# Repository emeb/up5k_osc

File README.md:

# up5k_osc
An FPGA-based digital oscillator for Eurorack

## What is it?
up5k_osc is a Eurorack-format digital oscillator demonstrating digital
audio synthesis with a low-cost FPGA. It supports several basic waveforms
commonly found in analog synthesizers, but generated digitally at very high
sample rates to avoid many of the problems with aliasing that occur when
these waveforms are synthesized at lower sample rates.

## Features
​
* 12HP wide 3U standard Eurorack module
* +/-12V supply on Doepfer-standard 16-pin shrouded, keyed header (30ma max)
* Trimmed 1V/Oct pitch control input with coarse and fine adjustment pots
* Attenuated Exponential FM input
* 3 additional uncommited +/-5V CV inputs with associated setting pots
* Sync input
* Two +/-5V range audio outputs
* Three 3 position toggles for range and mode control
* RGB LED indicator
* Additional single LED indicator
* USB-based firmware updates

## Design details
* Lattice iCE40 Ultra Plus 5k FPGA
* 4MB SPI Flash memory for configuration data, firmware and tables.
* 4-channel 12-bit SPI ADC with 500kSPS max sample rate
* Direct-access SPI Programming header
* 3-pin diagnostic header (2 data + ground)
* Reset and Bootloader pushbuttons
* Done Program LED
* Buck SMPS regulator for low current draw from +12V supply
* Differential PDM DACs for high-resolution, high sample rate and low THD audio

## Resources
* [Schematic](docs/up5k_osc_schematic.pdf)
* [BOM](docs/up5k_osc_bom.ods)

## Motivation
One of the most thorny issues encountered when attempting to synthesize simple
analog waveforms in the digital domain is that of aliasing which occurs due
to sharp transitions coupled with low sample rates. Seemingly "obvious" methods
of generating simple waveforms like sawtooths and square or pulse waves fail
miserably when the sharp edges of these waveforms jitter around due to the low
timing resolution of practical DSP sample rates. Mountains of research have been
devoted to DSP approaches to minimizing this edge jitter using techniques such
as BLIT, BLEP, MinBLEP, PolyBLEP, DPW, etc. These work, but end up becoming
compromises between the complexity of the approach (and the consequent CPU load
they impose) and the degree of alias rejection that they provide.

The brute-force approach is to synthesize these analog waveforms at sufficiently
high sample rates that the timing jitter becomes imperceptible. This is the
method that up5k_osc uses - an audio-rate oscillator is synthesized at sample
rates in excess of 10MHz which knocks the aliases of even the buzziest narrow
pulse wave down below 80dBfs. Differential Pulse Density Modulation is used to
do the digital-to-analog conversion in an inexpensive yet highly linear fashion.

## Theory of Operation
The up5k_osc system comprises a power supply, ADC, Flash Memory, FPGA and analog
I/O processing. 

### Power Supply
Eurorack systems typically provide +/-12V rails at a minimum, and as DSP becomes
a more common feature in typical racks, the +12V rails are disproportionally
loaded down by the use of simple LDO linear regulators to supply the high currents
needed by most modern digital components. up5k_osc uses a SMPS regulator module
to efficiently provide an internal 5V supply from which 3.3V analog and digital
supplys can be derived with less heat and waste.

### Analog Input Processing
A 4-channel 12-bit 500kSPS SPI ADC is used to digitize control voltage inputs
to the up5k_osc. One channel is dedicated to handling the typical 1V/Oct pitch
control and includes trimming to calibrate the 1V/Oct slope, as well as coarse
and fine user offsets as well as summing an attenuated FM input. This provides
roughly 2.7cents/lsb pitch resolution over a 10V range which covers most of
the musical range to an accuracy better than the commonly accepted human
perception.

The other three ADC channels are uncommitted CV inputs with offset controls and
a 10Vpp range. Running that the maximum rated conversion speed, the ADC can
provide 125kSPS per channel which is sufficiently high to provide good temporal
resolution.

### FPGA and SPI Flash
The Lattice iCE40 Ultra Plus 5k FPGA provides a modest gate count, a number of
useful hard IP cores, including SPI, I2C, Multiply-Accumulate and large RAM.
These resources are sufficient for reasonably complex DSP, soft processor cores
and I/O tasks. In the up5k_osc, the FPGA is loaded from the SPI Flash at power
up and immediately begins execution of a basic processing pipeline which begins
with driving a continuous stream of conversions from the ADC, formatting the
results for control of a fast internal NCO, waveshaping and then finally
generating the PDM output signals.

FPGA bitstreams, along with soft processor firmware and synthesis tables are
stored in the SPI flash. During development it's often simplest to directly load
the FPGA over the SPI configuration bus via a programming dongle and header on
the board, bypassing the SPI flash. In end-use situations however it's desirable
to have a simpler approach, and for that purpose a USB interface is provided
which uses the NO2 bootloader and the standardized DFU protocol to load data
into the SPI flash without extra hardware.

[NO2 Bootloader](https://github.com/no2fpga/no2bootloader)

The up5k_osc FPGA pinout for USB, SPI Flash and boot select button + LED has
been designed to follow that of the icebreaker bitsy, so building the
bootloader with that configuration will generate a usable bitstream.

### Switches and LEDs
User control options are provided in the form of three 3-position SPDT toggles
(on-off-on) which can be used to set pitch range, waveform types, etc. A few
LEDs are also provided to indicate operating conditions.

### Analog Outputs
Two PDM DACs are available with fully differential inputs from the FPGA to
improve linearity despite mismatches in rise & fall timing. A two-stage
lowpass reconstruction filter rolls off at about 30kHz, allowing harmonic
content well above normal human hearing range. SNR has been observed as better
that 90dBfs, THD for 1kHz sine is better than 80dBfs and with 16MSPS sample
rates the aliasing on naive sawtooth waveforms are lower than 80dBfs beyond
10kHz. Output levels of 10Vpp are compatible with common Eurorack standards.

## Gateware
Demonstration gateware for the up5k_osc is provided which handles all the basic
functions of an oscillator. Three pitch ranges are provided which cover rates
from 13min/cycle to 10kHz. Two output waveforms can be selected from among
sine/saw/pulse, with pulsewidth controlled by one of the CV inputs.

As delivered the demo gateware does not use a soft processor core. A serial
diagnostic output is generated by simple state machine logic to provide
observation of the ADC conversion results (formatted as 115k 8N1 serial). An
alternate build is possible via macro definitions in the source code that
enables a RISC-V core that can do more complex diagnostics, or even control
the oscillator with some imagination and more coding.

## Future Work
Going beyond this is certainly possible - wavetable morphing has been tested and
other synthesis techniques such as multi-operator FM are possible. The USB
interface could be employed to turn the module into an Audio class peripheral
that handles MIDI or PCM audio.

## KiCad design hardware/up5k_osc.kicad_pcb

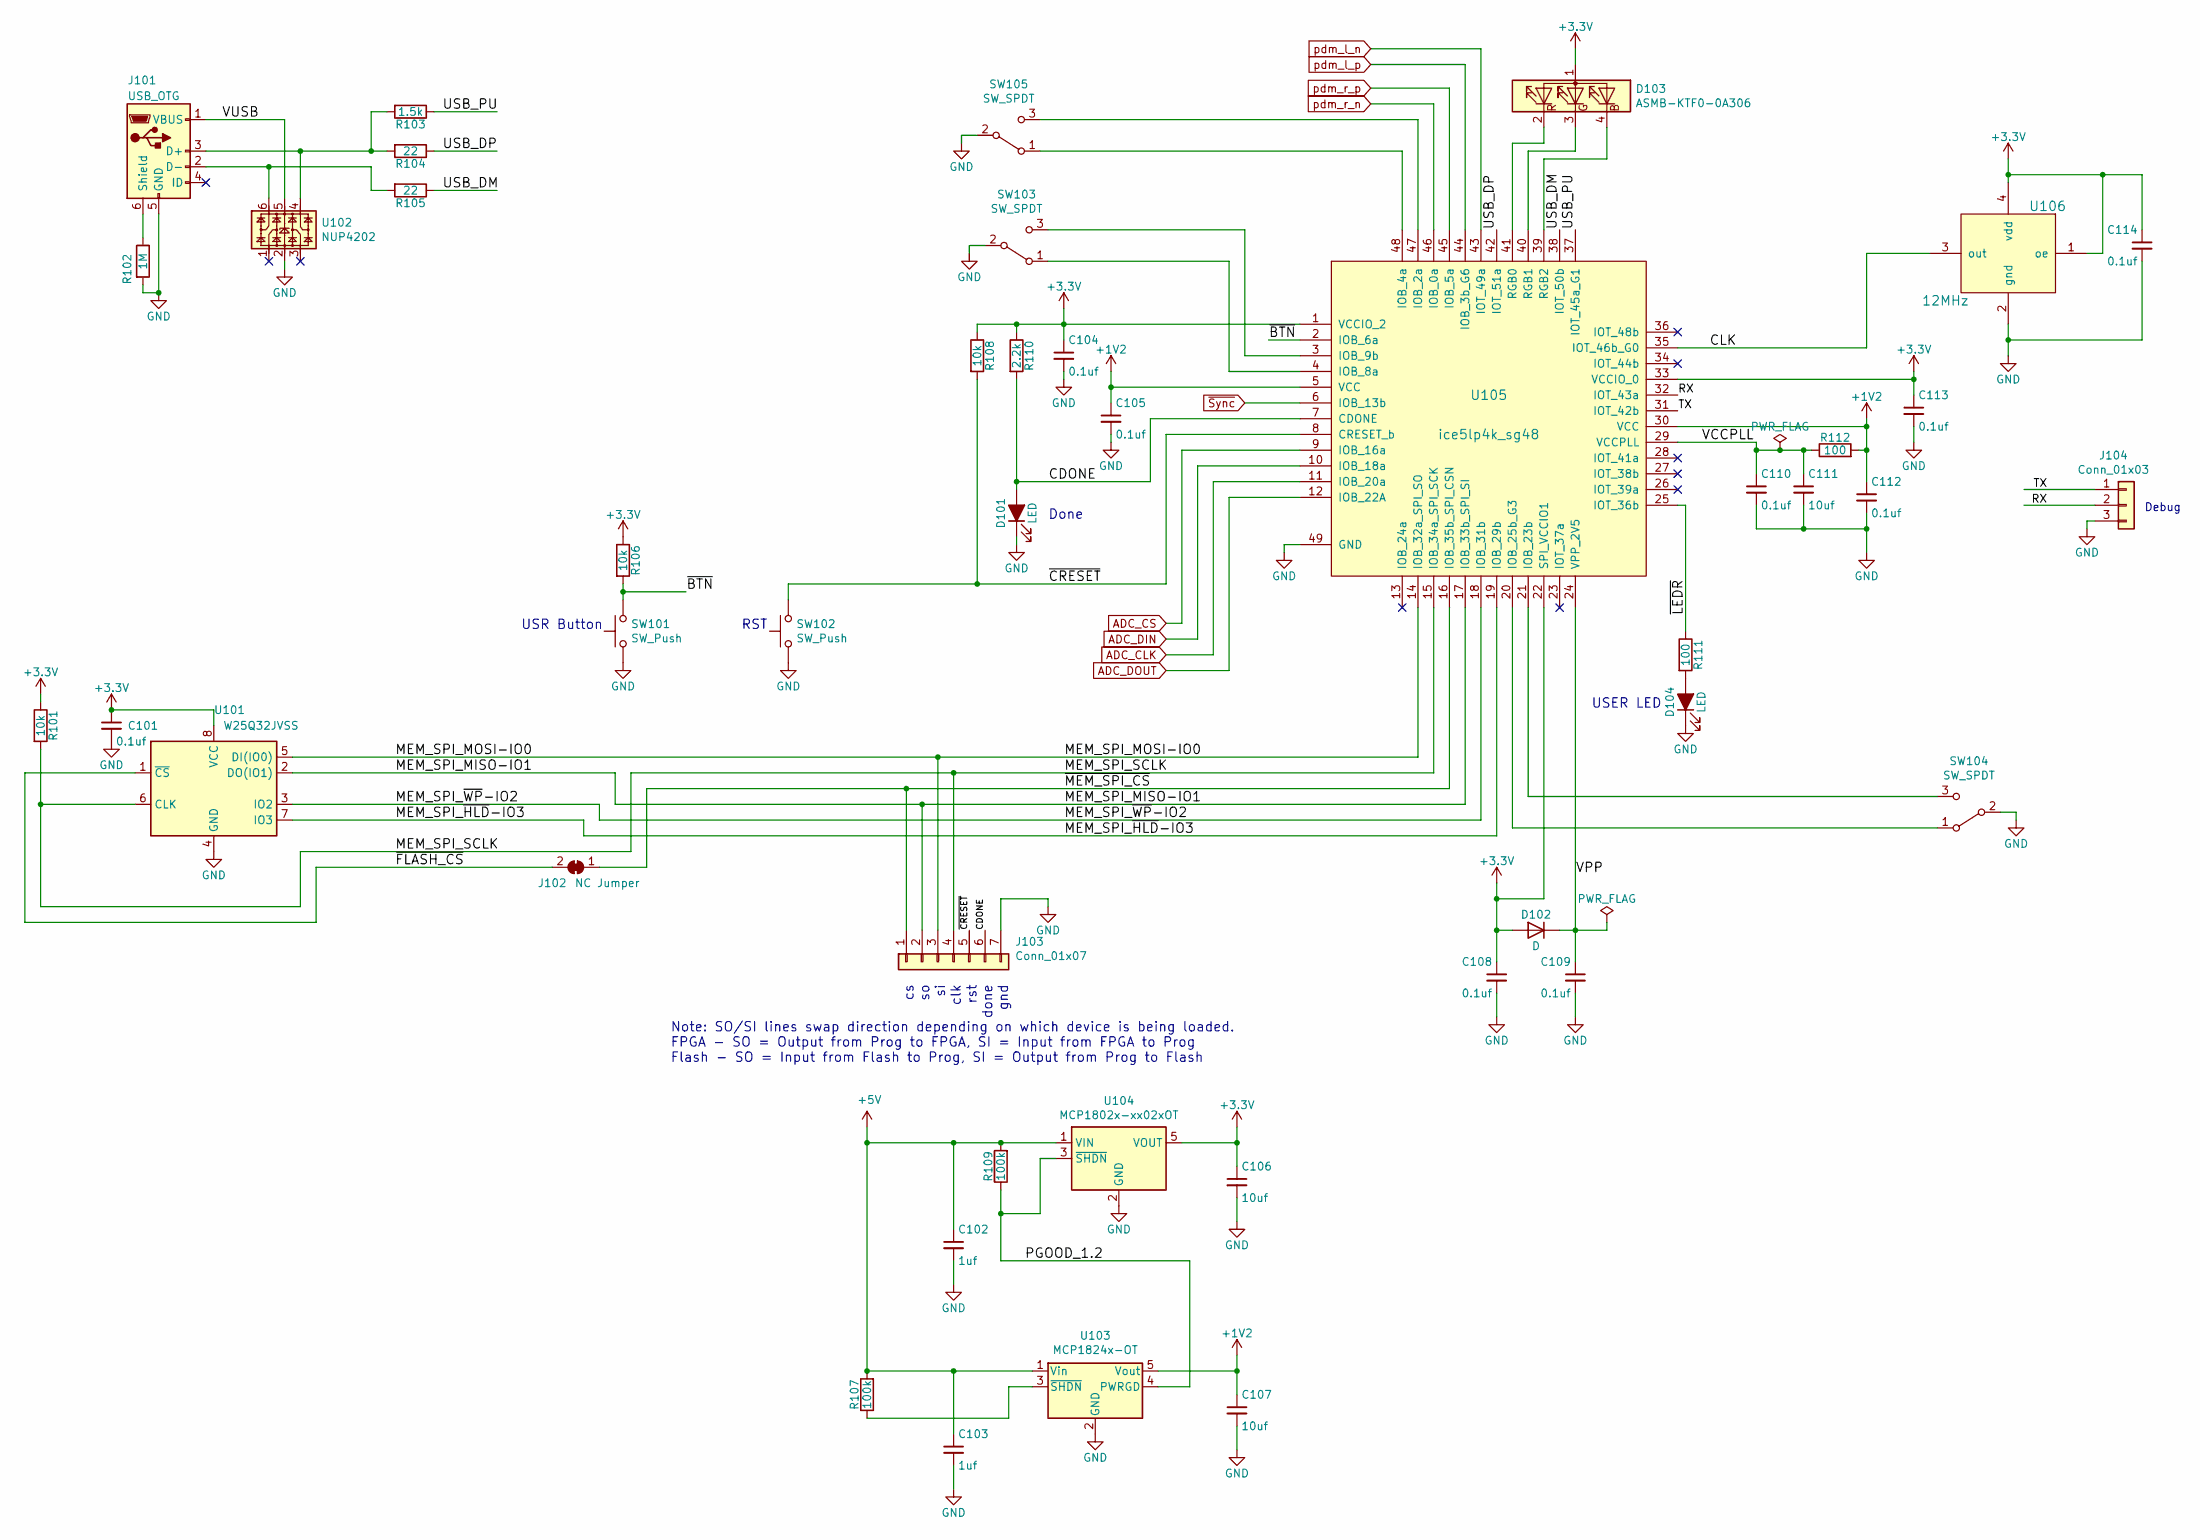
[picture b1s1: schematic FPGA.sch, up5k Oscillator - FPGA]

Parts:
C101, C104, C105, C108, C109, C110, C112, C113, C114: 0.1uf; C_0603
C102, C103: 1uf; C_0603
C106, C107, C111: 10uf; C_0805
D101, D104: LED; LED_0603
D102: D; D_0603
D103: ASMB-KTF0-0A306‎
J101: USB_OTG; USB_Micro-B_10103594-0001LF_actual_outline
J102: NC Jumper; SolderJumper-2_P1.3mm_Bridged_RoundedPad1.0x1.5mm
J103: Conn_01x07; Pin_Header_Straight_1x07_Pitch2.54mm
J104: Conn_01x03; Pin_Header_Straight_1x03_Pitch2.54mm
R101, R106, R108: 10k; R_0603
R102: 1M; R_0603
R103: 1.5k; R_0603
R104, R105: 22; R_0603
R107, R109: 100k; R_0603
R110: 2.2k; R_0603
R111, R112: 100; R_0603
SW101, SW102: SW_Push; SW_SPST_KMR2
SW103, SW104, SW105: SW_SPDT; SPDT_Submini
U101: W25Q32JVSS; SOIC-8_3.9x4.9mm_Pitch1.27mm
U102: NUP4202; SOT-23-6
U103: MCP1824x-OT; SOT-23-5
U104: MCP1802x-xx02xOT; SOT-23-5
U105: ice5lp4k_sg48; QFN-48-1EP_7x7mm_Pitch0.5mm_DIY_PADS
U106: 12MHz; Oscillator_SMD_SeikoEpson_SG210-4pin_2.5x2.0mm

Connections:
+1V2: C105.1, C107.1, C112.1, R112.2, U103.5 (Vout), U105.5 (VCC), U105.30 (VCC)
+3V3: C101.1, C104.1, C106.1, C108.1, C113.1, C114.1, D102.2 (A), D103.1 (A), R101.1, R106.1, R108.1, R110.1, U101.8 (VCC), U104.5 (VOUT), U105.1 (VCCIO_2), U105.22 (SPI_VCCIO1), U105.33 (VCCIO_0), U106.1 (oe), U106.4 (vdd); also elsewhere on the board
+5V: C102.1, C103.1, R107.2, R109.2, U103.1 (Vin), U104.1 (VIN); also elsewhere on the board
/Sheet60703823/CDONE: D101.2 (A), J103.6, R110.2, U105.7 (CDONE)
/Sheet60703823/CLK: U105.35 (IOT_46b_G0), U106.3 (out)
/Sheet60703823/MEM_SPI_MISO-IO1: J103.2, U101.2 (DO(IO1)), U105.17 (IOB_33b_SPI_SI)
/Sheet60703823/MEM_SPI_MOSI-IO0: J103.3, U101.5 (DI(IO0)), U105.14 (IOB_32a_SPI_SO)
/Sheet60703823/MEM_SPI_SCLK: J103.4, R101.2, U101.6 (CLK), U105.15 (IOB_34a_SPI_SCK)
/Sheet60703823/MEM_SPI_~HLD~-IO3: U101.7 (IO3), U105.19 (IOB_29b)
/Sheet60703823/MEM_SPI_~WP~-IO2: U101.3 (IO2), U105.18 (IOB_31b)
/Sheet60703823/PGOOD_1.2: R109.1, U103.4 (PWRGD), U104.3 (~SHDN)
/Sheet60703823/RX: J104.2, U105.32 (IOT_43a)
/Sheet60703823/TX: J104.1, U105.31 (IOT_42b)
/Sheet60703823/USB_DM: R105.1, U105.38 (IOT_50b)
/Sheet60703823/USB_DP: R104.1, U105.42 (IOT_51a)
/Sheet60703823/USB_PU: R103.1, U105.37 (IOT_45a_G1)
/Sheet60703823/VCCPLL: C110.1, C111.1, R112.1, U105.29 (VCCPLL)
/Sheet60703823/VPP: C109.1, D102.1 (K), U105.24 (VPP_2V5)
/Sheet60703823/VUSB: J101.1 (VBUS), U102.5
/Sheet60703823/~BTN: R106.2, SW101.2, U105.2 (IOB_6a)
/Sheet60703823/~CRESET: J103.5, R108.2, SW102.2, U105.8 (CRESET_b)
/Sheet60703823/~FLASH_CS: J102.2 (B), U101.1 (~CS)
/Sheet60703823/~LEDR: R111.1, U105.25 (IOT_36b)
/Sheet60703823/~MEM_SPI_CS: J102.1 (A), J103.1, U105.16 (IOB_35b_SPI_CSN)
ADC_CLK: U105.11 (IOB_20a); also elsewhere on the board
ADC_CS: U105.9 (IOB_16a); also elsewhere on the board
ADC_DIN: U105.10 (IOB_18a); also elsewhere on the board
ADC_DOUT: U105.12 (IOB_22A); also elsewhere on the board
GND: C101.2, C102.2, C103.2, C104.2, C105.2, C106.2, C107.2, C108.2, C109.2, C110.2, C111.2, C112.2, C113.2, C114.2, D101.1 (K), D104.1 (K), J101.5 (GND), J103.7, J104.3, R102.2, SW101.1, SW102.1, SW103.2 (B), SW104.2 (B), SW105.2 (B), U101.4 (GND), U102.2, U103.2 (GND), U104.2 (GND), U105.49 (GND), U106.2 (gnd); also elsewhere on the board
unnamed: D103.2 (RK), U105.41 (RGB0)
unnamed: D103.3 (GK), U105.40 (RGB1)
unnamed: D103.4 (BK), U105.39 (RGB2)
unnamed: D104.2 (A), R111.2
unnamed: J101.2 (D-), R105.2, U102.6
unnamed: J101.3 (D+), R103.2, R104.2, U102.4
unnamed: J101.6 (Shield), R102.1
unnamed: R107.1, U103.3 (~SHDN)
unnamed: SW103.1 (A), U105.4 (IOB_8a)
unnamed: SW103.3 (C), U105.3 (IOB_9b)
unnamed: SW104.1 (A), U105.20 (IOB_25b_G3)
unnamed: SW104.3 (C), U105.21 (IOB_23b)
unnamed: SW105.1 (A), U105.48 (IOB_4a)
unnamed: SW105.3 (C), U105.47 (IOB_2a)
pdm_l_n: U105.43 (IOT_49a); also elsewhere on the board
pdm_l_p: U105.44 (IOB_3b_G6); also elsewhere on the board
pdm_r_n: U105.46 (IOB_0a); also elsewhere on the board
pdm_r_p: U105.45 (IOB_5a); also elsewhere on the board
~Sync: U105.6 (IOB_13b); also elsewhere on the board

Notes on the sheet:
clk
rst
done
gnd
Done
Note: SO/SI lines swap direction depending on which device is being loaded. FPGA - SO = Output from Prog to FPGA, SI = Input from FPGA to Prog Flash - SO = Input from Flash to Prog, SI = Output from Prog to Flash
RST
USR Button
USER LED
Debug

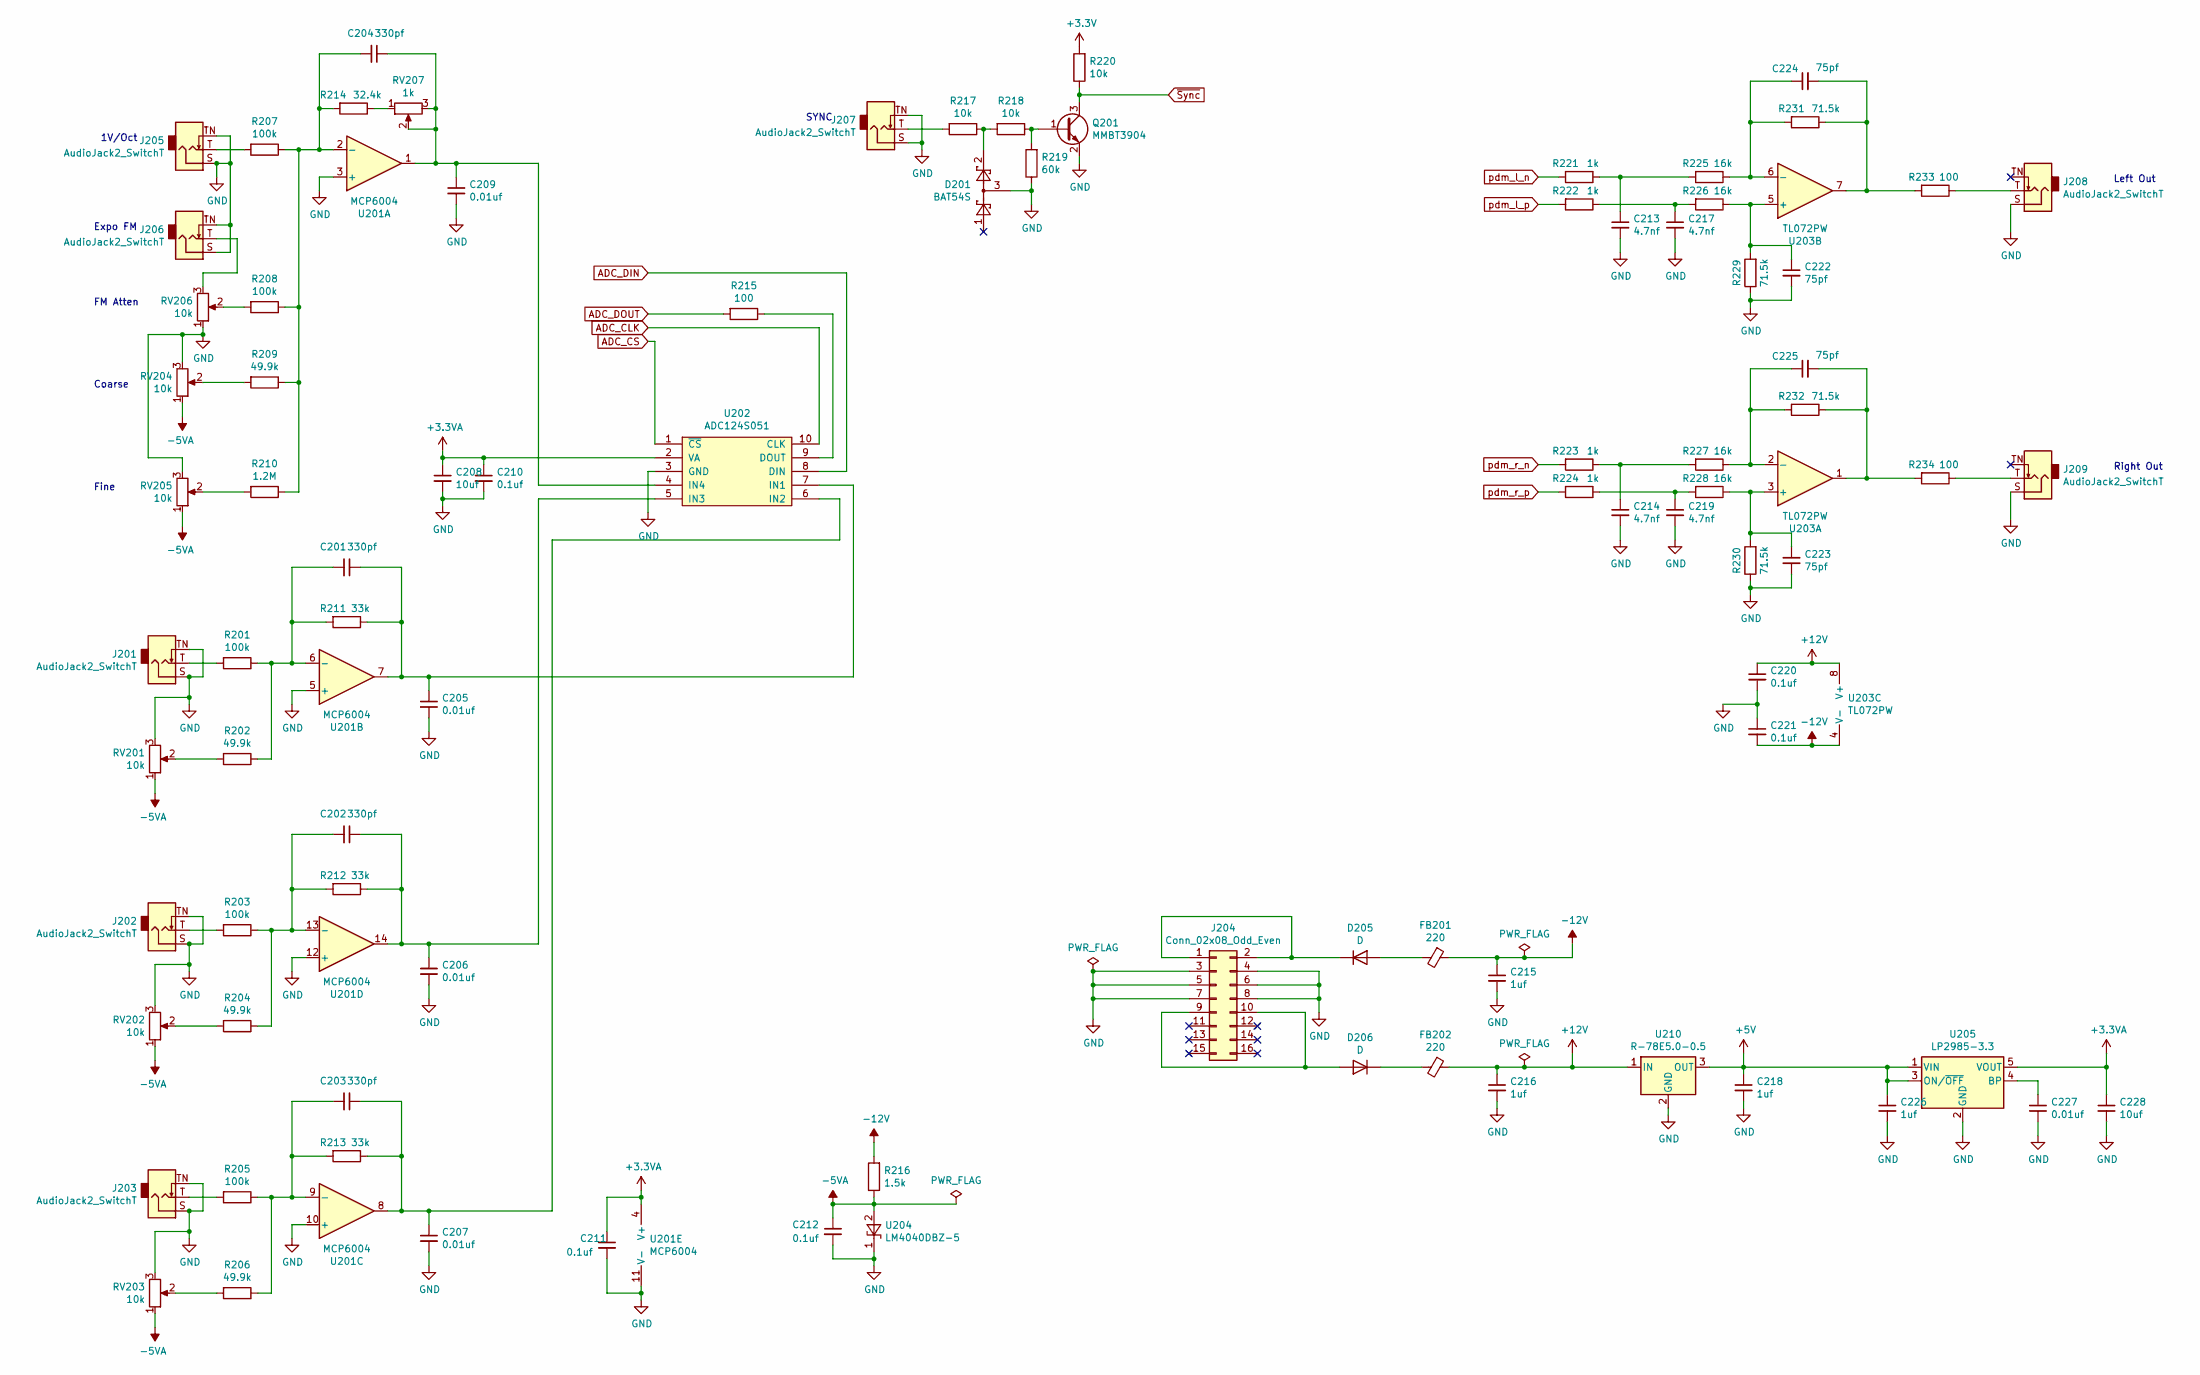
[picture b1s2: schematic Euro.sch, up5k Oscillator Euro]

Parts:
C201, C202, C203, C204: 330pf; C_0603
C205, C206, C207, C209, C227: 0.01uf; C_0603
C208, C228: 10uf; C_0805
C210, C211, C212, C220, C221: 0.1uf; C_0603
C213, C214, C217, C219: 4.7nf; C_0603
C215, C216, C218, C226: 1uf; C_0603
C222, C223, C224, C225: 75pf; C_0603
D201: BAT54S; SOT-23
D205, D206: D; D_SMA
FB201, FB202: 220; R_0805
J201, J202, J203, J205, J206, J207, J208, J209: AudioJack2_SwitchT; Jack_3.5mm_QingPu_WQP-PJ398SM_Vertical_CircularHoles
J204: Conn_02x08_Odd_Even; 5103308-3
Q201: MMBT3904; SOT-23
R201, R203, R205, R207, R208: 100k; R_0603
R202, R204, R206, R209: 49.9k; R_0603
R210: 1.2M; R_0603
R211, R212, R213: 33k; R_0603
R214: 32.4k; R_0603
R215, R233, R234: 100; R_0603
R216: 1.5k; R_0603
R217, R218, R220: 10k; R_0603
R219: 60k; R_0603
R221, R222, R223, R224: 1k; R_0603
R225, R226, R227, R228: 16k; R_0603
R229, R230, R231, R232: 71.5k; R_0603
RV201, RV202, RV203, RV204, RV205, RV206: 10k; Potentiometer_TT_P0915N
RV207: 1k; 23BR500LFTR
U201: MCP6004; TSSOP-14_4.4x5mm_Pitch0.65mm
U202: ADC124S051; MSOP-10_3x3mm_Pitch0.5mm
U203: TL072PW; TSSOP-8_4.4x3mm_Pitch0.65mm
U204: LM4040DBZ-5; SOT-23
U205: LP2985-3.3; SOT-23-5
U210: R-78E5.0-0.5; Converter_DCDC_RECOM_R-78E-0.5_THT

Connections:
+3.3VA: C208.1, C210.1, C211.1, C228.1, U201.4 (V+), U202.2 (VA), U205.5 (VOUT)
+3V3: R220.2; also elsewhere on the board
+5V: C218.1, C226.1, U205.1 (VIN), U205.3 (ON/~OFF~), U210.3 (OUT); also elsewhere on the board
+12V: C216.1, C220.1, FB202.1, U203.8 (V+), U210.1 (IN)
-5VA: C212.1, R216.1, RV201.1, RV202.1, RV203.1, RV204.1, RV205.1, U204.2 (A)
-12V: C215.1, C221.2, FB201.1, R216.2, U203.4 (V-)
ADC_CLK: U202.10 (CLK); also elsewhere on the board
ADC_CS: U202.1 (~CS); also elsewhere on the board
ADC_DIN: U202.8 (DIN); also elsewhere on the board
ADC_DOUT: R215.2; also elsewhere on the board
GND: C205.2, C206.2, C207.2, C208.2, C209.2, C210.2, C211.2, C212.2, C213.2, C214.2, C215.2, C216.2, C217.2, C218.2, C219.2, C220.2, C221.1, C222.2, C223.2, C226.2, C227.2, C228.2, D201.3, J201.S, J201.TN, J202.S, J202.TN, J203.S, J203.TN, J204.3, J204.4, J204.5, J204.6, J204.7, J204.8, J205.S, J205.TN, J206.S, J206.TN, J207.S, J207.TN, J208.S, J209.S, Q201.2 (E), R219.1, R229.1, R230.1, RV201.3, RV202.3, RV203.3, RV204.3, RV205.3, RV206.1, U201.3 (+), U201.5 (+), U201.10 (+), U201.11 (V-), U201.12 (+), U202.3 (GND), U204.1 (K), U205.2 (GND), U210.2 (GND); also elsewhere on the board
unnamed: C201.1, C205.1, R211.1, U201.7, U202.7 (IN1)
unnamed: C201.2, R201.1, R202.1, R211.2, U201.6 (-)
unnamed: C202.1, C206.1, R212.1, U201.14, U202.5 (IN3)
unnamed: C202.2, R203.1, R204.1, R212.2, U201.13 (-)
unnamed: C203.1, C207.1, R213.1, U201.8, U202.6 (IN2)
unnamed: C203.2, R205.1, R206.1, R213.2, U201.9 (-)
unnamed: C204.1, C209.1, RV207.2, RV207.3, U201.1, U202.4 (IN4)
unnamed: C204.2, R207.1, R208.1, R209.1, R210.1, R214.2, U201.2 (-)
unnamed: C213.1, R221.1, R225.2
unnamed: C214.1, R223.1, R227.2
unnamed: C217.1, R222.1, R226.2
unnamed: C219.1, R224.1, R228.2
unnamed: C222.1, R226.1, R229.2, U203.5 (+)
unnamed: C223.1, R228.1, R230.2, U203.3 (+)
unnamed: C224.1, R225.1, R231.2, U203.6 (-)
unnamed: C224.2, R231.1, R233.2, U203.7
unnamed: C225.1, R227.1, R232.2, U203.2 (-)
unnamed: C225.2, R232.1, R234.2, U203.1
unnamed: C227.1, U205.4 (BP)
unnamed: D201.2, R217.1, R218.2
unnamed: D205.1 (K), J204.1, J204.2
unnamed: D205.2 (A), FB201.2
unnamed: D206.1 (K), FB202.2
unnamed: D206.2 (A), J204.9, J204.10
unnamed: J201.T, R201.2
unnamed: J202.T, R203.2
unnamed: J203.T, R205.2
unnamed: J205.T, R207.2
unnamed: J206.T, RV206.3
unnamed: J207.T, R217.2
unnamed: J208.T, R233.1
unnamed: J209.T, R234.1
unnamed: Q201.1 (B), R218.1, R219.2
unnamed: R202.2, RV201.2
unnamed: R204.2, RV202.2
unnamed: R206.2, RV203.2
unnamed: R208.2, RV206.2
unnamed: R209.2, RV204.2
unnamed: R210.2, RV205.2
unnamed: R214.1, RV207.1
unnamed: R215.1, U202.9 (DOUT)
pdm_l_n: R221.2; also elsewhere on the board
pdm_l_p: R222.2; also elsewhere on the board
pdm_r_n: R223.2; also elsewhere on the board
pdm_r_p: R224.2; also elsewhere on the board
~Sync: Q201.3 (C), R220.1; also elsewhere on the board

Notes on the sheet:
1V/Oct
Expo FM
Coarse
Fine
FM Atten
Left Out
Right Out
SYNC

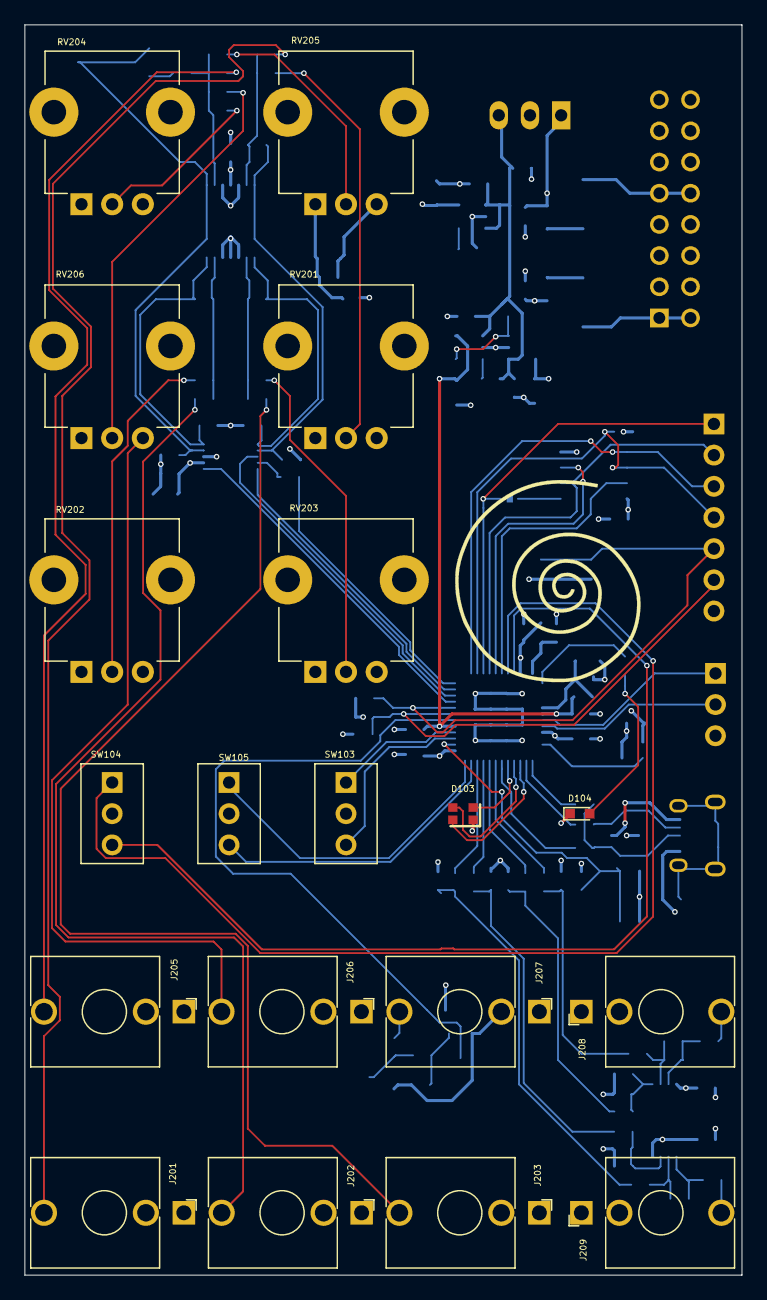
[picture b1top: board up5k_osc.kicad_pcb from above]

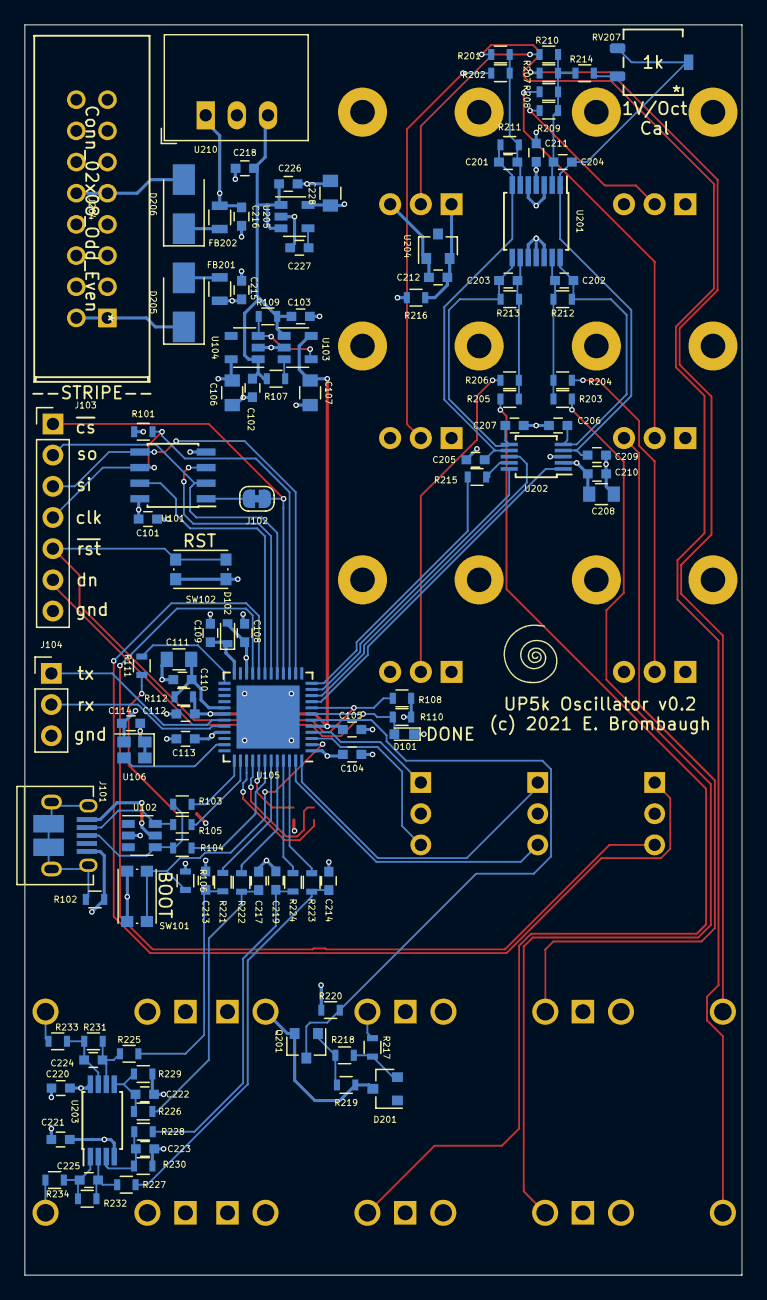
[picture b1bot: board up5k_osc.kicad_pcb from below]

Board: 4 copper layers, 58.4 x 101.9 mm, 137 parts (117 on the bottom side), 93 nets.

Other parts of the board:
Ref**: Val**; avatar_small
Ref**#2: Val**; avatar

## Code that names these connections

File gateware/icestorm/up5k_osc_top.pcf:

# Pin assignments for up5k_osc project

set_io clk_12 35

set_io adc_si  10
set_io adc_so  12
set_io adc_clk 11
set_io adc_cs  9

set_io pdm_l_p 44
set_io pdm_l_n 43
set_io pdm_r_p 45
set_io pdm_r_n 46

set_io RGB0 39
set_io RGB1 40
set_io RGB2 41

set_io LEDR 25

set_io rx 32
set_io tx 31

set_io SYNC 6

#set_io BTN 2

set_io -pullup yes SW103[0] 3
set_io -pullup yes SW103[1] 4

set_io -pullup yes SW104[0] 21
set_io -pullup yes SW104[1] 20

set_io -pullup yes SW105[0] 47
set_io -pullup yes SW105[1] 48

#set_io MEM_SPI_MOSI_IO0 14
#set_io MEM_SPI_SCLK 15
#set_io MEM_SPI_CS 16
#set_io MEM_SPI_MISO_IO1 17
#set_io MEM_SPI_WP_IO2 18
#set_io MEM_SPI_HLD_IO3 19

#set_io usb_dp 42
#set_io usb_dn 38
#set_io usb_pu 37

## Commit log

2021-06-26 Initial commit of hardware and gateware
2021-06-26 Add picorv32 submodule
2021-06-26 Added documentation
2021-06-26 Added photos
2021-06-26 Fix typos
2021-06-27 Add some more text

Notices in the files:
hardware/up5k_osc.kicad_pcb:
(c) 2021 E. Brombaugh
parts and their libraries:
Copyright 2016 Accelerated Designs. All rights reserved.
